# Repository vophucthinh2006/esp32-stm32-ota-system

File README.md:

# ESP32 to STM32 Dual-MCU OTA Update System

A robust dual-MCU Firmware Over-The-Air (OTA) update system. This project utilizes an ESP32 as a network-connected gateway that fetches firmware binaries from a GitHub repository via HTTPS and flashes them onto an STM32F103C8T6 target microcontroller via a custom bare-metal UART bootloader protocol.

---

## 1. Project Overview

This system provides a reliable, remote firmware deployment pipeline for distributed edge devices. The architecture clearly separates the network gateway layer from the core application execution layer:

* **ESP32 (Gateway):** Periodically polls GitHub using HTTPS HEAD requests, monitors the `ETag` header for remote binary changes, streams 128-byte chunk buffers over SSL, and acts as the UART Master to program the host.
* **STM32F103 (Application Host):** Runs a custom **Bare-Metal Bootloader** (direct register access) that verifies a 2-step handshake, erases designated internal flash pages, calculates 16-bit CRC on incoming packets, programs internal flash, and safely jumps to user application space.

---

## 2. Key Features & Implementation Achievements

* **Dynamic Update Detection:** Uses HTTP `ETag` tracking instead of full binary downloads to detect remote firmware updates, drastically reducing bandwidth and power consumption.
* **Cache-Busting Mechanism:** Appends a random `cache buster` parameter to query URLs to bypass proxy/CDN caching and guarantee fresh fetches.
* **Bare-Metal Reliability:** The STM32 bootloader is implemented entirely at the register level (No HAL, No LL, No RTOS), minimizing code footprint and eliminating library overhead.
* **Stream-Based Chunk Buffering:** Downloads and flashes firmware in 128-byte chunks, avoiding the need for large external flash/RAM storage.
* **Memory-Safe Padding:** Automates 128-byte alignment padding (`0xFF`) for non-full partial flash blocks at the end of the stream.
* **Hardware Status Indicators:** Dedicated LEDs provide real-time visual feedback (`LED_POWER`, `LED_NEW_VERSION`, `LED_LOADING`).

---

## 3. Hardware Overview & Pinout

### 3.1 Components & Modules
* **Gateway Microcontroller:** ESP32-DevKitC-32D.
* **Target Microcontroller:** STM32F103C8T6 (ARM Cortex-M3).
* **Power Management:** LM2596 Buck Converter Module (12V Battery Input → 5V System Power).
* **Power Control:** SW_SPDT Power Switch.
* **User Input:** SPST Push Button with RC filter (`C1 = 0.1µF`) for physical debouncing.

### 3.2 Pin Mapping

#### ESP32 Gateway Board:
| Pin Name | Function / Connection | Description |
| :--- | :--- | :--- |
| `IO32` | `LED_POWER` (`D1` via 220Ω) | Power-On Indicator |
| `IO17` | `LED_NEW_VERSION` (`D2` via 220Ω) | Remote update available on GitHub |
| `IO2` | `LED_LOADING` (`D3` via 220Ω) | Active flashing/erasing in progress |
| `IO4` | `SW1 Button` (Active-Low) | User trigger to start OTA update process |
| `TXD2` (`IO10`) | UART2 TX $\rightarrow$ STM32 RX | Serial Command & Payload Line |
| `RXD2` (`IO9`) | UART2 RX $\leftarrow$ STM32 TX | Serial ACK/NACK Response Line |

#### Target Communication Header (5-Pin Header):
| Pin | Function | Description |
| :--- | :--- | :--- |
| `1` | `VCC` | +5V Power Rail |
| `2` | `GND` | Ground Reference |
| `3` | `RxD` | UART Receive Line |
| `4` | `TxD` | UART Transmit Line |
| `5` | `Button` | Manual Boot Mode Trigger / Hardware Interlock |

---

## 4. Hardware Design & Schematics

### 4.1 Schematic Diagram
The custom carrier board schematic integrates power regulation, status LEDs, debounced input, and external headers.

### 4.2 PCB Layout
Single-sided PCB design incorporating power planes, signal routing, and modular sub-board connections.

---

## 5. Software Architecture & State Machines

### 5.1 System-Level Finite State Machine (End-to-End Workflow)
The complete interaction lifecycle between GitHub Cloud, ESP32 Gateway, and STM32 Target Microcontroller:

### 5.2 STM32 Bootloader Internal Operations
Detailed internal state processing, packet verification, and flash memory execution on the target STM32:

---

## 6. UART Communication Protocol

All control frames and data packets transmitted from the ESP32 to the STM32 adhere to a structured protocol format:

### 6.1 Packet Structure
| Field | Size (Bytes) | Description / Value |
| :--- | :--- | :--- |
| **Start of Frame (SOF)** | 2 | Header Sync Bytes: `0xAA 0xBB` |
| **Command Code (CMD)** | 1 | `0x01` (START), `0x02` (ERASE), `0x03` (PROGRAM), `0x04` (JUMP) |
| **Data Length** | 1 | Payload byte length ($N \le 250$) |
| **Payload Data** | $N$ | Binary firmware slice or command parameters |
| **Checksum (CRC16)** | 2 | Big-Endian CCITT CRC-16 ($x^{16} + x^{12} + x^5 + 1$) |

### 6.2 Security Handshake Sequence
Before accepting flashing commands, the STM32 enforces a strict key validation handshake:
1. ESP32 sends `BL_UPDATE_KEY_1` (`0xCC`). STM32 validates and responds with `ACK` (`0x0A`).
2. ESP32 sends `BL_UPDATE_KEY_2` (`0xDD`). STM32 validates and responds with `ACK` (`0x0A`).
3. Upon completion, STM32 transitions to the verified bootloader receiving state.

### 6.3 Flashing Commands Breakdown
* `BL_START` (`0x01`): Resets internal flash write pointer (`FLASH_Page_Pointer`) to `APP_ADD_BASE` (`0x08002000`).
* `BL_ERASE` (`0x02`): Sequentially erases target application pages (Pages 8 to 63).
* `BL_PROGRAM` (`0x03`): Programs incoming 128-byte binary streams into Flash as 16-bit half-words and increments the memory pointer.
* `BL_JUMP` (`0x04`): Disables global interrupts, re-maps Vector Table (`SCB_VTOR` to `0x08002000`), sets Main Stack Pointer (`_Set_MSP`), and jumps to User Application Execution.

---

## 7. Flash Memory Mapping (STM32F103C8T6)

The internal 64KB Flash memory space is divided to segregate the immutable bootloader from the upgradable application space:

---

## 8. Demo Video
Below is a short demo video illustrating the end-to-end OTA update process:

▶️ [ESP32 to STM32 Dual-MCU OTA Update - Demo Video](https://youtu.be/XsSUUxfZz8Y?si=K6gj_BpSvMdLIf3Q)

---

## 9. Build and Flash
**ESP32 Gateway Firmware**
* **Framework: ESP-IDF / Arduino Core for ESP32.**

* **Libraries:** WiFiClientSecure, HTTPClient.

**STM32 Bootloader**
* **Toolchain:** arm-none-eabi-gcc.

* **Build System:** CMake.

* **Programmer:** ST-Link V2.

* **Development Style:** Bare-metal direct register programming (No HAL / LL libraries used).

---

## 10. Performance & System Trade-offs
* **Baud Rate Selection (9600 bps):** Chosen to guarantee noise-immune, zero-error serial data transfer over unshielded wires between the gateway and target board without needing hardware RTS/CTS flow control.

* **Stream Buffering vs. External Storage:** Processing firmware in small 128-byte RAM buffers eliminates the physical footprint, cost, and power overhead of an external SPI Flash chip or SD card module.

* **Single-Bank Flashing:** Prioritizes maximum flash allocation for user applications (~56KB available out of 64KB) over dual-bank storage, relying on CRC checks and handshake verification to ensure update integrity.

---

## 11. Limitations and Future Improvements
* **Dual-Bank Architecture:** Adding external SPI flash to support rollback in case of power interruption during programming.

* **Hardware Reset Line:** Wiring an ESP32 GPIO directly to the STM32 NRST pin for automated hard-resets into bootloader mode.

* **Firmware Encryption:** Implementing AES-128/256 payload decryption on the STM32 to secure firmware against eavesdropping.

---

## 12. Author
**Author:** Vo Phuc Thinh

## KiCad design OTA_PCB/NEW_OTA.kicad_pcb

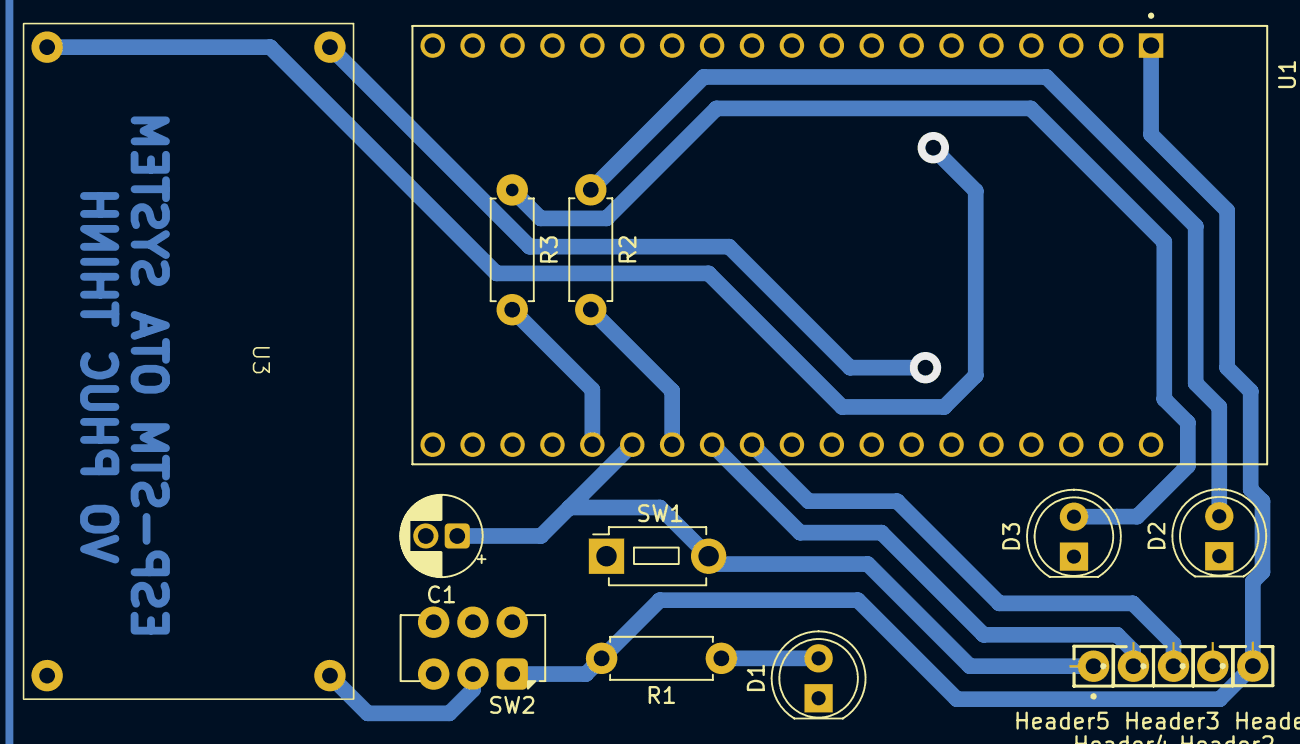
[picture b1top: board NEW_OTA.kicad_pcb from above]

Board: 2 copper layers, 16 parts (0 on the bottom side), 11 nets.

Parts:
C1: 0.1uF; CP_Radial_D5.0mm_P2.00mm
D1, D2, D3: LED; LED_D5.0mm_Clear
Header1: VCC; SAMTEC_MTLW-101-08-S-S-330
Header2: GND; SAMTEC_MTLW-101-08-S-S-330
Header3: RXD; SAMTEC_MTLW-101-08-S-S-330
Header4: TXD; SAMTEC_MTLW-101-08-S-S-330
Header5: Button; SAMTEC_MTLW-101-08-S-S-330
R1, R2, R3: 220; R_Axial_DIN0207_L6.3mm_D2.5mm_P7.62mm_Horizontal
SW1: Button; SW_PUSH_1P1T_6x3.5mm_H4.3_APEM_MJTP1243
SW2: SW_SPDT; SW_CK_JS202011AQN_DPDT_Angled
U1: ESP32-DEVKITC-32D; MODULE_ESP32-DEVKITC-32D
U3: LM2596-Buck-Converter-Module; LM2596 Buck Converter Module

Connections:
/Button: C1.1, Header5.01 (01_01), SW1.1, U1.J3-14 (IO0)
/Source: SW2.2 (B), U3.1 (OUT+)
/UART2_RX: Header4.01 (01_01), U1.J3-12 (IO16)
/UART2_TX: Header3.01 (01_01), U1.J3-11 (IO17)
/VCC: Header1.01 (01_01), R1.2, SW2.1 (A), U1.J2-1 (3V3)
GND: C1.2, D1.1 (K), D2.1 (K), D3.1 (K), Header2.01 (01_01), SW1.2, U1.J2-14 (GND1), U1.J3-1 (GND3), U1.J3-7 (GND2), U3.2 (OUT-)
unnamed: D1.2 (A), R1.1
unnamed: D2.2 (A), R2.1
unnamed: D3.2 (A), R3.1
unnamed: R3.2, U1.J3-15 (IO2)
unnamed: R2.2, U1.J3-13 (IO4)

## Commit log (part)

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2026-04-29 downloading test
2026-04-30 Update testing file
2026-04-30 NEW UPDATE
2026-04-30 OTA Update %date% %time%
2026-05-06 Init: add STM code files
2026-05-06 Delete .gitignore
    Delete: STM .gitignore file
2026-05-06 Fix: Remove submodule and successfully add BOOTLOADER source files
2026-05-06 Init: Add ESP code files.
2026-05-06 Finalize project structure: Move bin file and update gitignore
2026-05-06 Update firmware 2026-05-07 05:42:06
2026-05-06 Update firmware 2026-05-07 05:51:49
2026-05-06 Update firmware 2026-05-07 05:55:43
2026-05-07 Update firmware 2026-05-07 13:22:39
2026-05-07 Update firmware 2026-05-07 13:25:40
2026-05-07 Update firmware 2026-05-07 14:02:05
2026-05-26 Update comments and ensure string termination
2026-06-21 Update firmware 2026-06-21 08:21:14
2026-06-21 Update firmware 2026-06-21 08:27:57
2026-06-21 Update firmware 2026-06-21 09:08:09
